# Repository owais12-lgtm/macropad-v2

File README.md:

# About

this is my second macropad im making, it has 15 programable keys a encoder and oled screen! 

# Pictures

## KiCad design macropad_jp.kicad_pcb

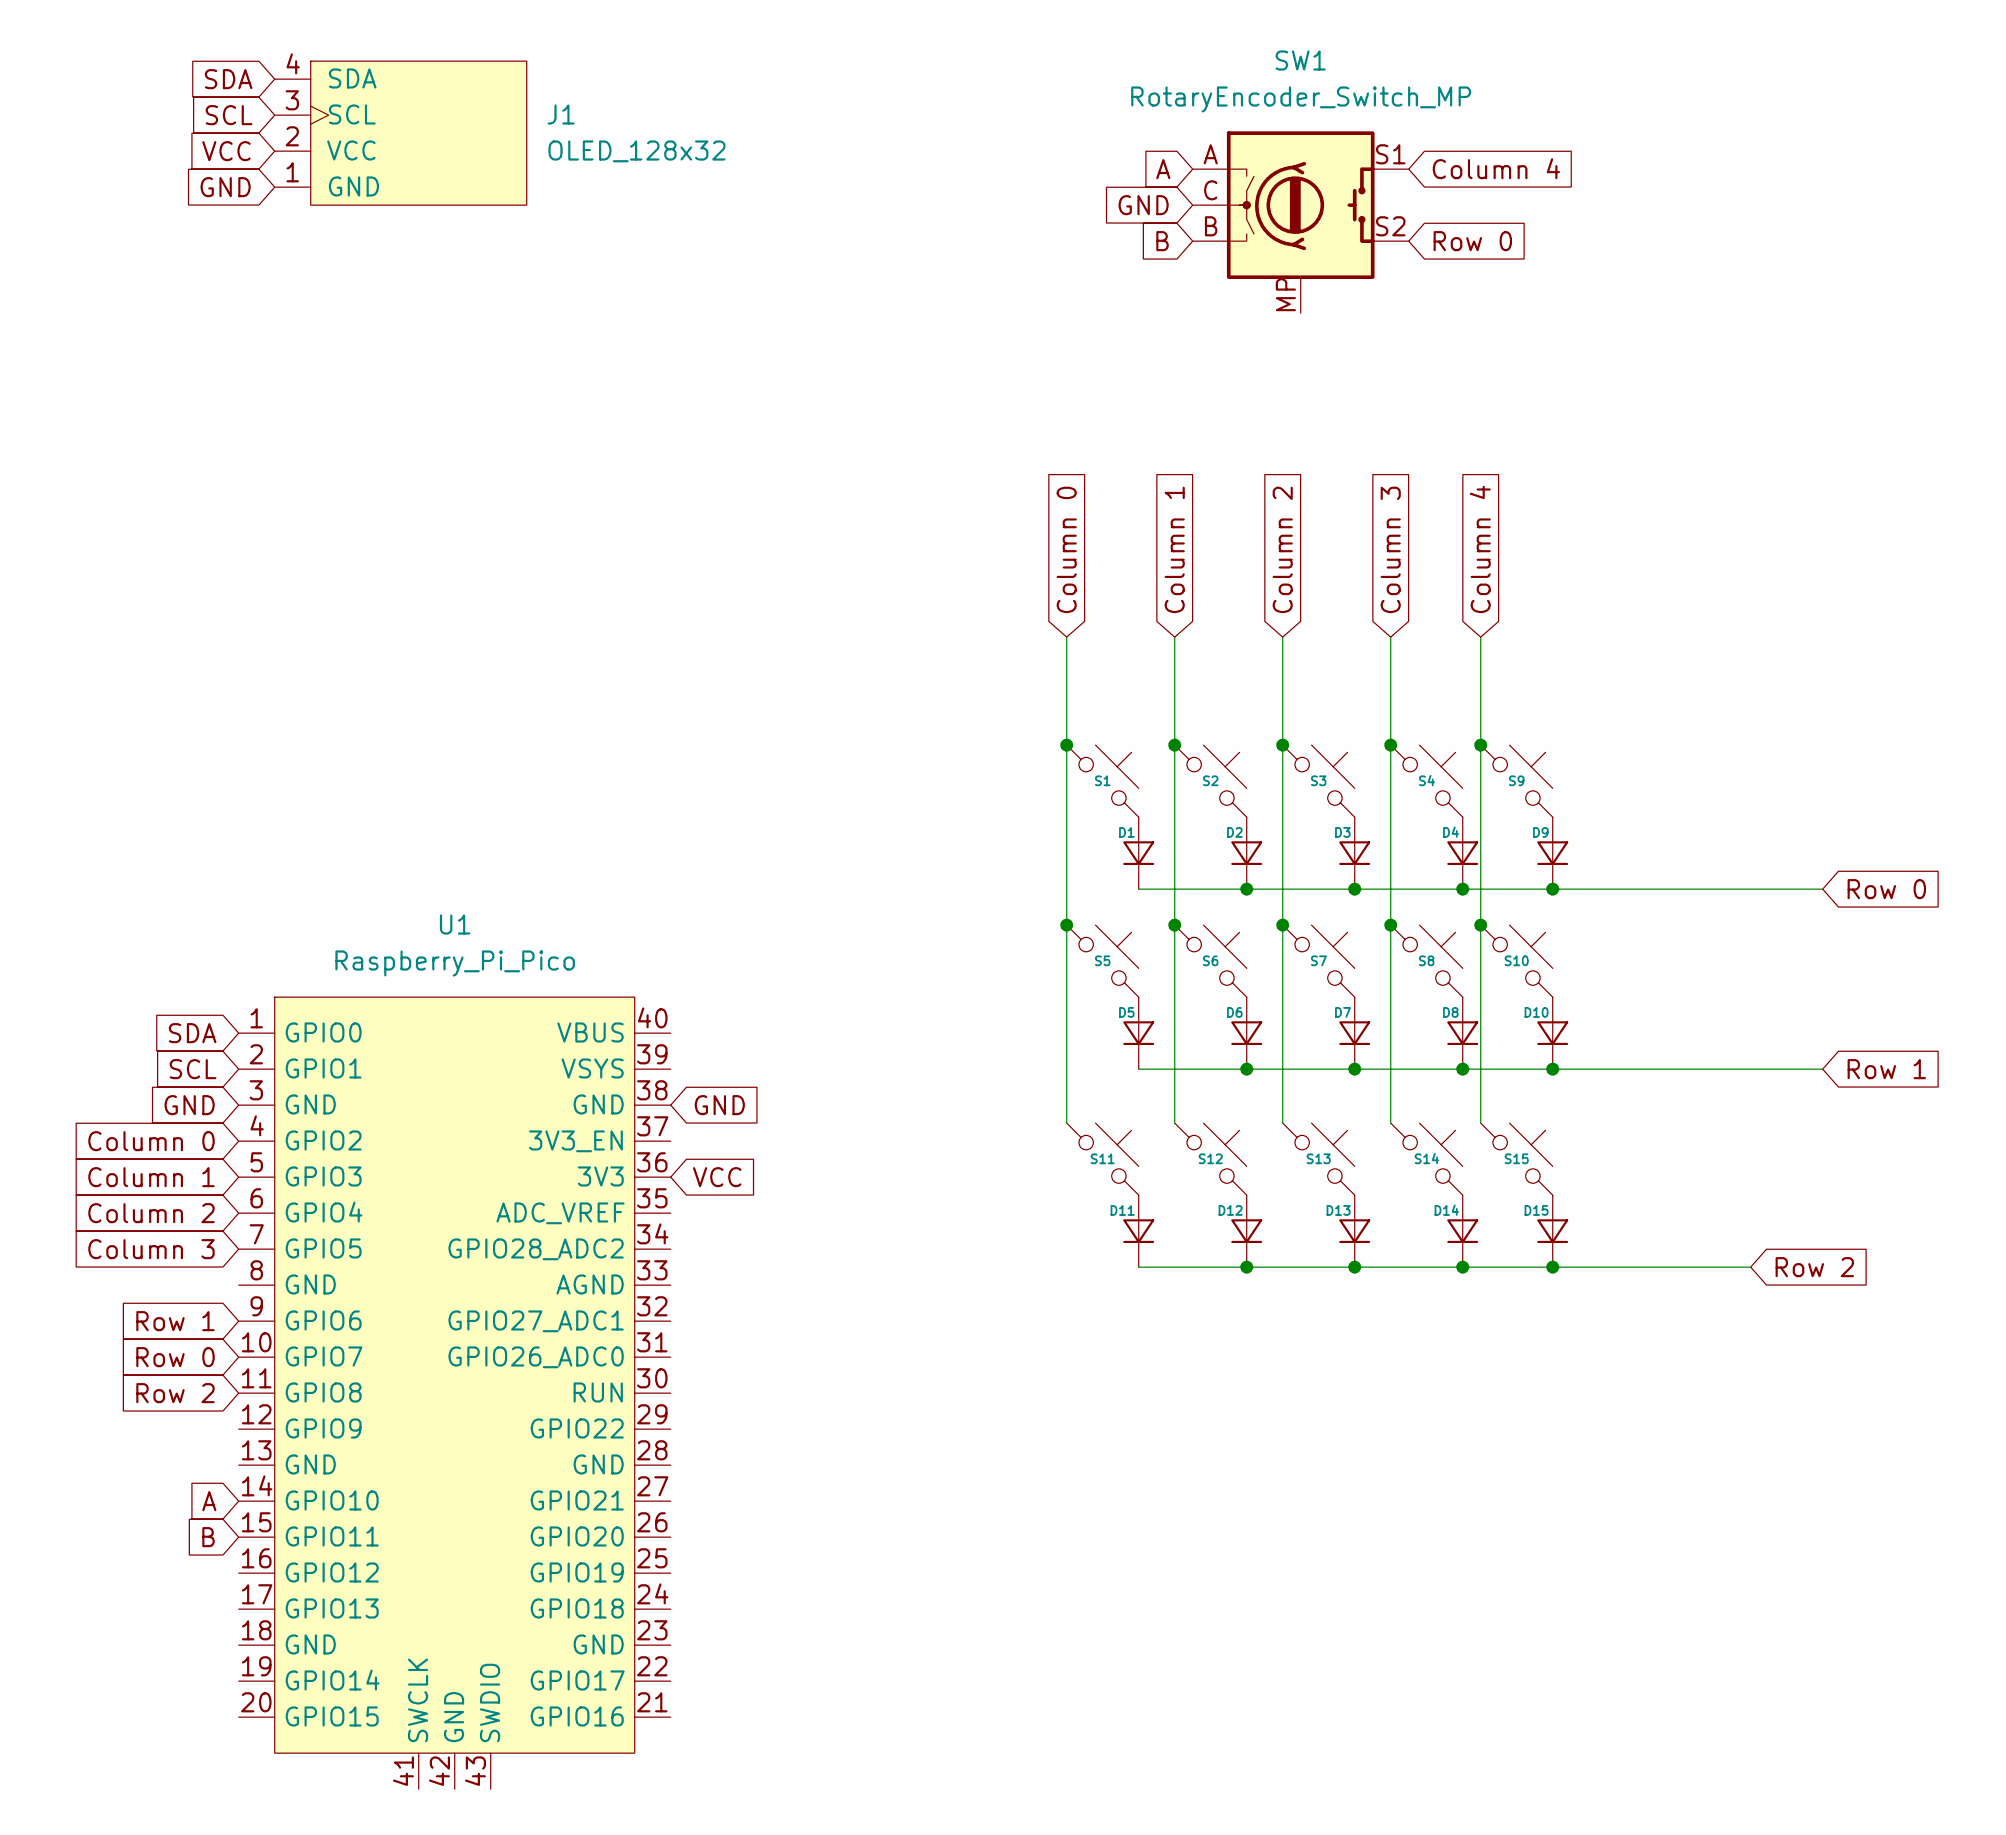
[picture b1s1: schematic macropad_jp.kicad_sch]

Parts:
D1, D2, D3, D4, D5, D6, D7, D8, D9, D10, D11, D12, D13, D14, D15: Diode_DO-35
J1: OLED_128x32
S1, S2, S3, S4, S5, S6, S7, S8, S9, S10, S11, S12, S13, S14, S15: MX_PCB_1.00u
SW1: RotaryEncoder_Switch_MP; RotaryEncoder_Alps_EC11E-Switch_Vertical_H20mm
U1: Raspberry_Pi_Pico

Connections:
A: SW1.A, U1.14 (GPIO10)
B: SW1.B, U1.15 (GPIO11)
Column 0: S1.1, S5.1, S11.1, U1.4 (GPIO2)
Column 1: S2.1, S6.1, S12.1, U1.5 (GPIO3)
Column 2: S3.1, S7.1, S13.1, U1.6 (GPIO4)
Column 3: S4.1, S8.1, S14.1, U1.7 (GPIO5)
Column 4: S9.1, S10.1, S15.1, SW1.S1
GND: J1.1 (GND), SW1.C, U1.3 (GND), U1.38 (GND)
unnamed: D1.2 (A), S1.2
unnamed: D2.2 (A), S2.2
unnamed: D3.2 (A), S3.2
unnamed: D4.2 (A), S4.2
unnamed: D5.2 (A), S5.2
unnamed: D6.2 (A), S6.2
unnamed: D7.2 (A), S7.2
unnamed: D8.2 (A), S8.2
unnamed: D9.2 (A), S9.2
unnamed: D10.2 (A), S10.2
unnamed: D11.2 (A), S11.2
unnamed: D12.2 (A), S12.2
unnamed: D13.2 (A), S13.2
unnamed: D14.2 (A), S14.2
unnamed: D15.2 (A), S15.2
Row 0: D1.1 (K), D2.1 (K), D3.1 (K), D4.1 (K), D9.1 (K), SW1.S2, U1.10 (GPIO7)
Row 1: D5.1 (K), D6.1 (K), D7.1 (K), D8.1 (K), D10.1 (K), U1.9 (GPIO6)
Row 2: D11.1 (K), D12.1 (K), D13.1 (K), D14.1 (K), D15.1 (K), U1.11 (GPIO8)
SCL: J1.3 (SCL), U1.2 (GPIO1)
SDA: J1.4 (SDA), U1.1 (GPIO0)
VCC: J1.2 (VCC), U1.36 (3V3)

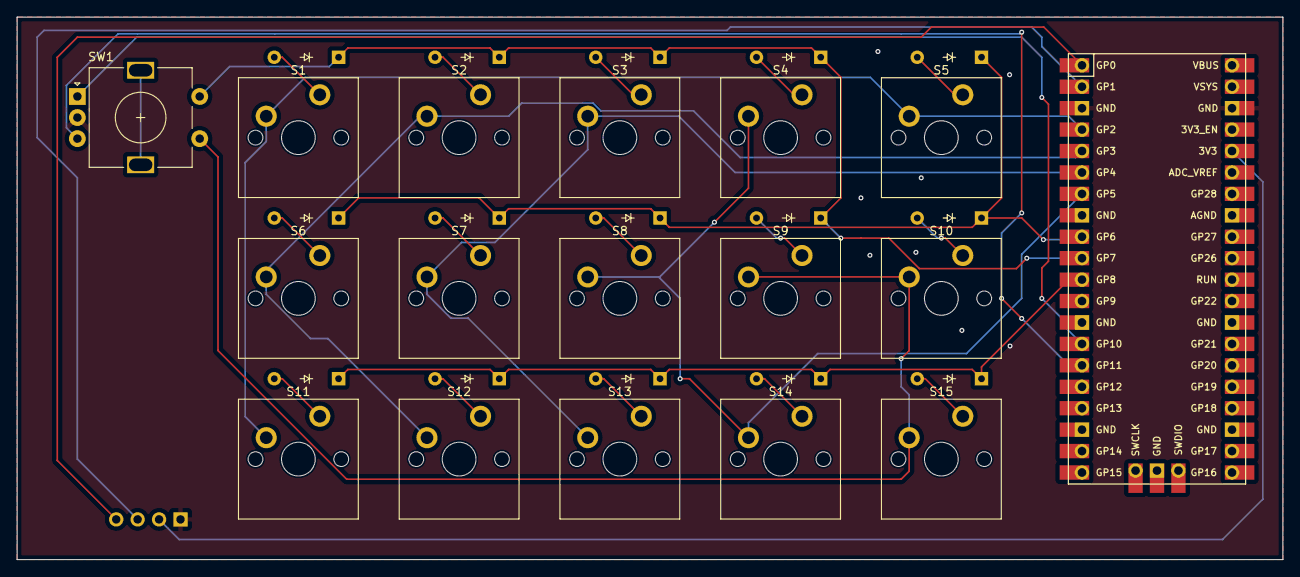
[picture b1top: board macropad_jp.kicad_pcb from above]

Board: 2 copper layers, 150.0 x 64.3 mm, 33 parts (0 on the bottom side), 29 nets.
